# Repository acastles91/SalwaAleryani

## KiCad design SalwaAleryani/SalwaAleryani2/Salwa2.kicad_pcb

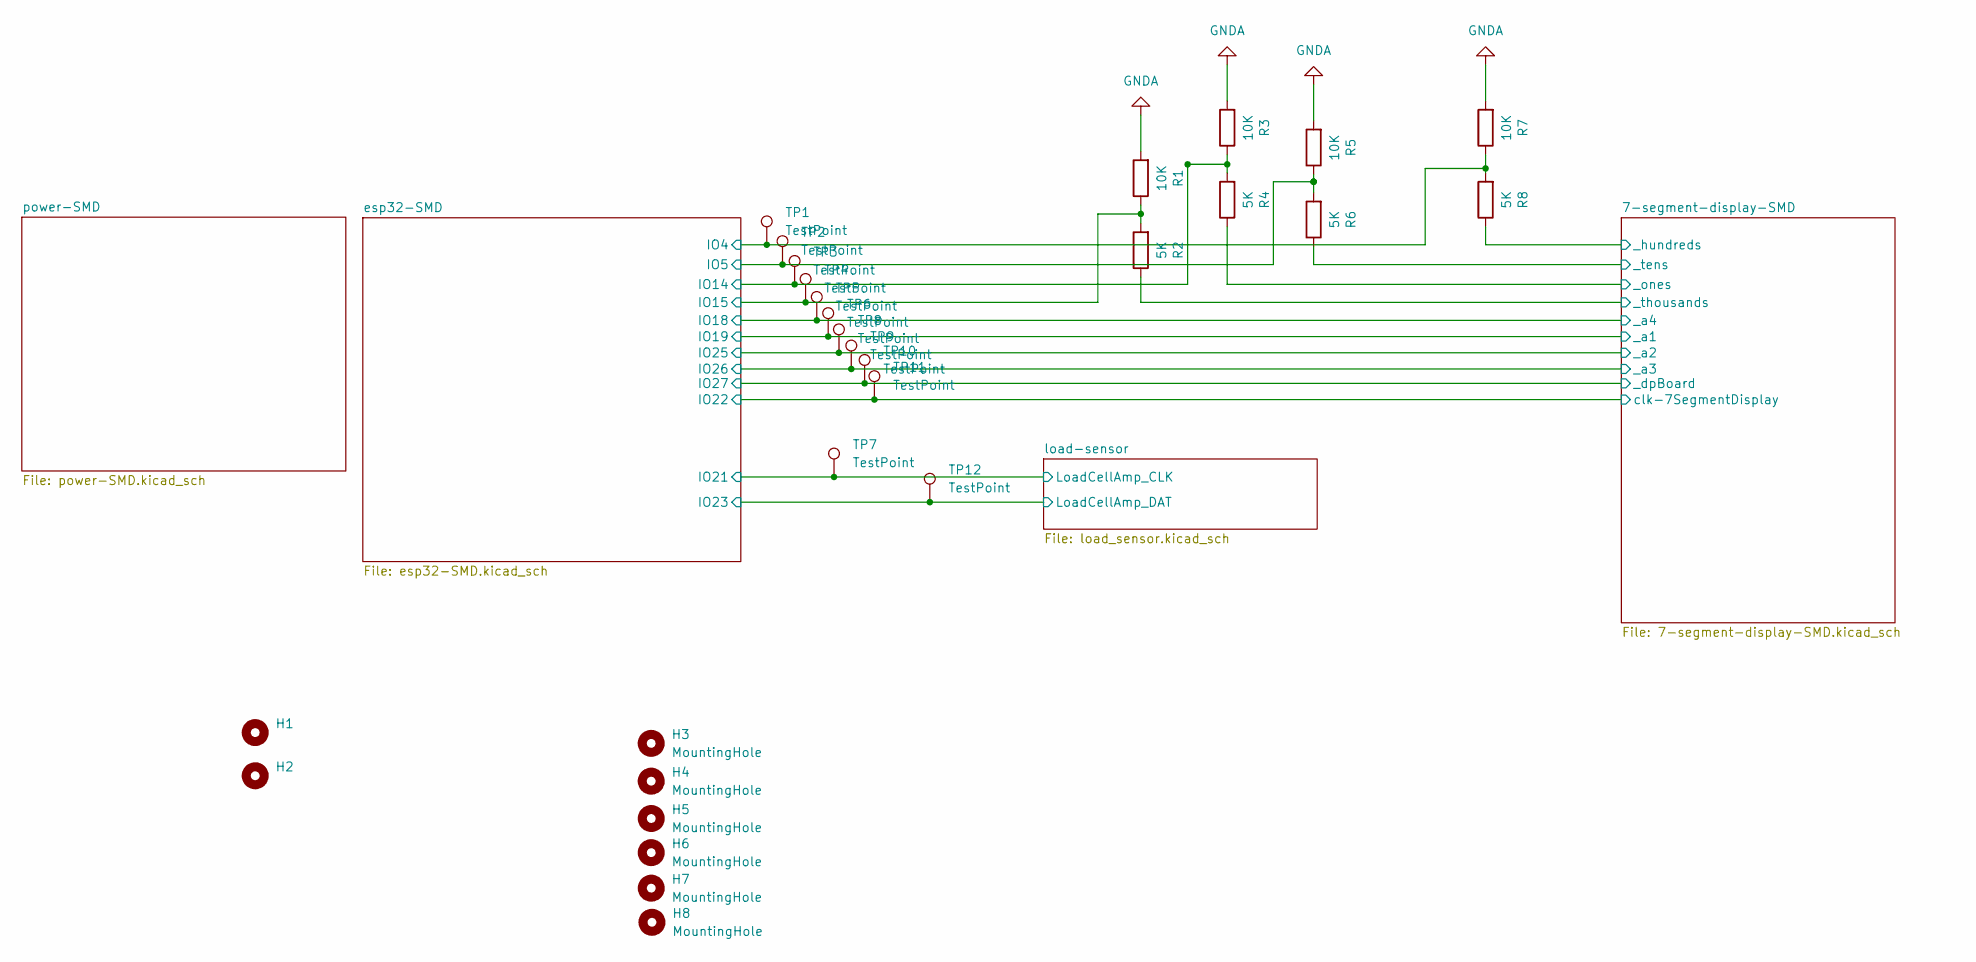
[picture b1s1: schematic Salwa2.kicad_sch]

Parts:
H1, H2: (no value)
H3, H4, H5, H6, H7, H8: MountingHole; MountingHole_4.3mm_M4_Pad_Via
R1, R3, R5, R7: 10K; R_1206_3216Metric_Pad1.30x1.75mm_HandSolder
R2, R4, R6, R8: 5K; R_1206_3216Metric_Pad1.30x1.75mm_HandSolder
TP1, TP2, TP3, TP4, TP5, TP6, TP7, TP8, TP9, TP10, TP11, TP12: TestPoint; TestPoint_Loop_D2.50mm_Drill1.85mm

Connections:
/7-segment-display-SMD/BCD_in1: TP6.1; also elsewhere on the board
/7-segment-display-SMD/BCD_in2: TP8.1; also elsewhere on the board
/7-segment-display-SMD/BCD_in3: TP9.1; also elsewhere on the board
/7-segment-display-SMD/BCD_in4: TP5.1; also elsewhere on the board
/7-segment-display-SMD/_dpBoard: TP10.1; also elsewhere on the board
/7-segment-display-SMD/_hundreds: R8.1; also elsewhere on the board
/7-segment-display-SMD/_ones: R4.1; also elsewhere on the board
/7-segment-display-SMD/_tens: R6.1; also elsewhere on the board
/7-segment-display-SMD/_thousands: R2.1; also elsewhere on the board
/7-segment-display-SMD/clk-7SegmentDisplay: TP11.1; also elsewhere on the board
/esp32-SMD/IO4: R7.1, R8.2, TP1.1; also elsewhere on the board
/esp32-SMD/IO5: R5.1, R6.2, TP2.1; also elsewhere on the board
/esp32-SMD/IO14: R3.1, R4.2, TP3.1; also elsewhere on the board
/esp32-SMD/IO15: R1.1, R2.2, TP4.1; also elsewhere on the board
/esp32-SMD/IO21: TP7.1; also elsewhere on the board
/esp32-SMD/IO23: TP12.1; also elsewhere on the board
GNDA: R1.2, R3.2, R5.2, R7.2; also elsewhere on the board

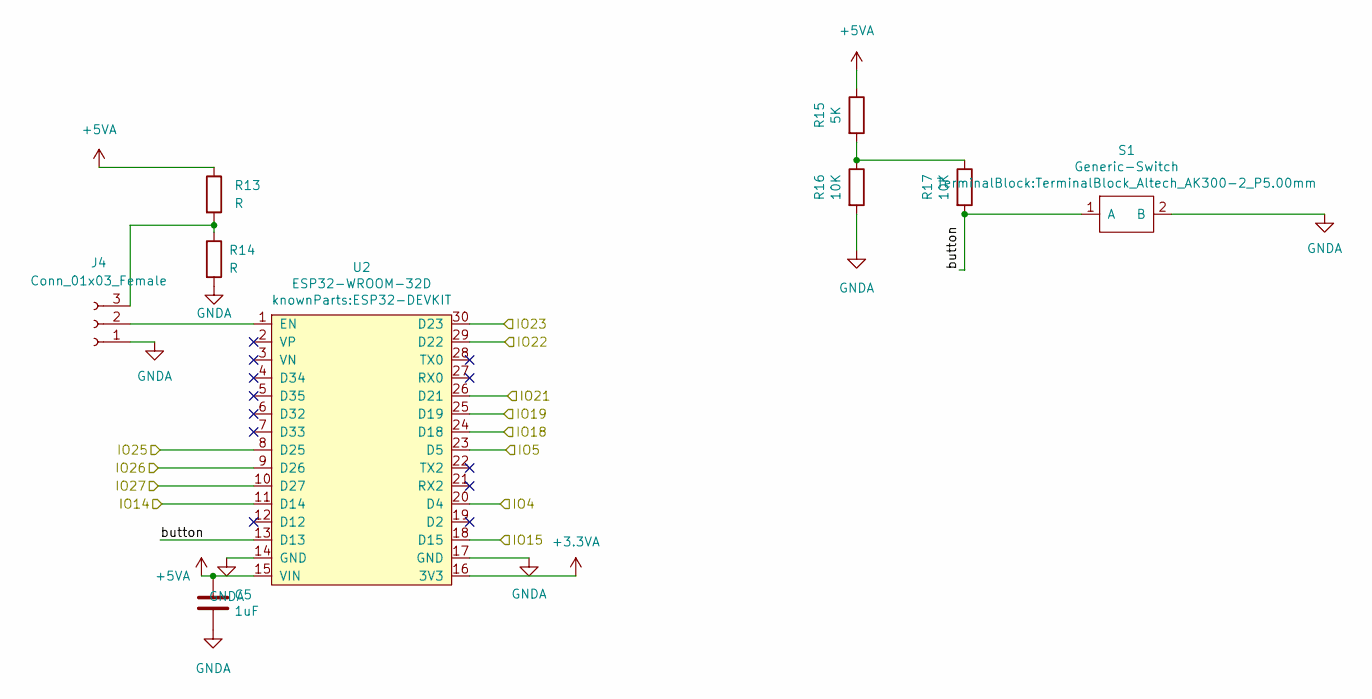
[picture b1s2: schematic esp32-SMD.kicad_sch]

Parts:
C5: 1uF; C_1210_3225Metric_Pad1.33x2.70mm_HandSolder
J4: Conn_01x03_Female; PinHeader_1x03_P2.54mm_Vertical
R13, R14: R; R_1206_3216Metric_Pad1.30x1.75mm_HandSolder
R15: 5K; R_1206_3216Metric_Pad1.30x1.75mm_HandSolder
R16, R17: 10K; R_1206_3216Metric_Pad1.30x1.75mm_HandSolder
S1: Generic-Switch; TerminalBlock_Altech_AK300-2_P5.00mm
U2: ESP32-WROOM-32D; ESP32-DEVKIT

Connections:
+3.3VA: U2.16 (3V3); also elsewhere on the board
+5VA: C5.1, R13.1, R15.1, U2.15 (VIN); also elsewhere on the board
/7-segment-display-SMD/BCD_in1: U2.25 (D19); also elsewhere on the board
/7-segment-display-SMD/BCD_in2: U2.8 (D25); also elsewhere on the board
/7-segment-display-SMD/BCD_in3: U2.9 (D26); also elsewhere on the board
/7-segment-display-SMD/BCD_in4: U2.24 (D18); also elsewhere on the board
/7-segment-display-SMD/_dpBoard: U2.10 (D27); also elsewhere on the board
/7-segment-display-SMD/clk-7SegmentDisplay: U2.29 (D22); also elsewhere on the board
/esp32-SMD/IO4: U2.20 (D4); also elsewhere on the board
/esp32-SMD/IO5: U2.23 (D5); also elsewhere on the board
/esp32-SMD/IO14: U2.11 (D14); also elsewhere on the board
/esp32-SMD/IO15: U2.18 (D15); also elsewhere on the board
/esp32-SMD/IO21: U2.26 (D21); also elsewhere on the board
/esp32-SMD/IO23: U2.30 (D23); also elsewhere on the board
/esp32-SMD/button: R17.2, S1.1 (A), U2.13 (D13)
GNDA: C5.2, J4.1, R14.2, R16.2, S1.2 (B), U2.14 (GND), U2.17 (GND); also elsewhere on the board
unnamed: J4.2, U2.1 (EN)
unnamed: J4.3, R13.2, R14.1
unnamed: R15.2, R16.1, R17.1

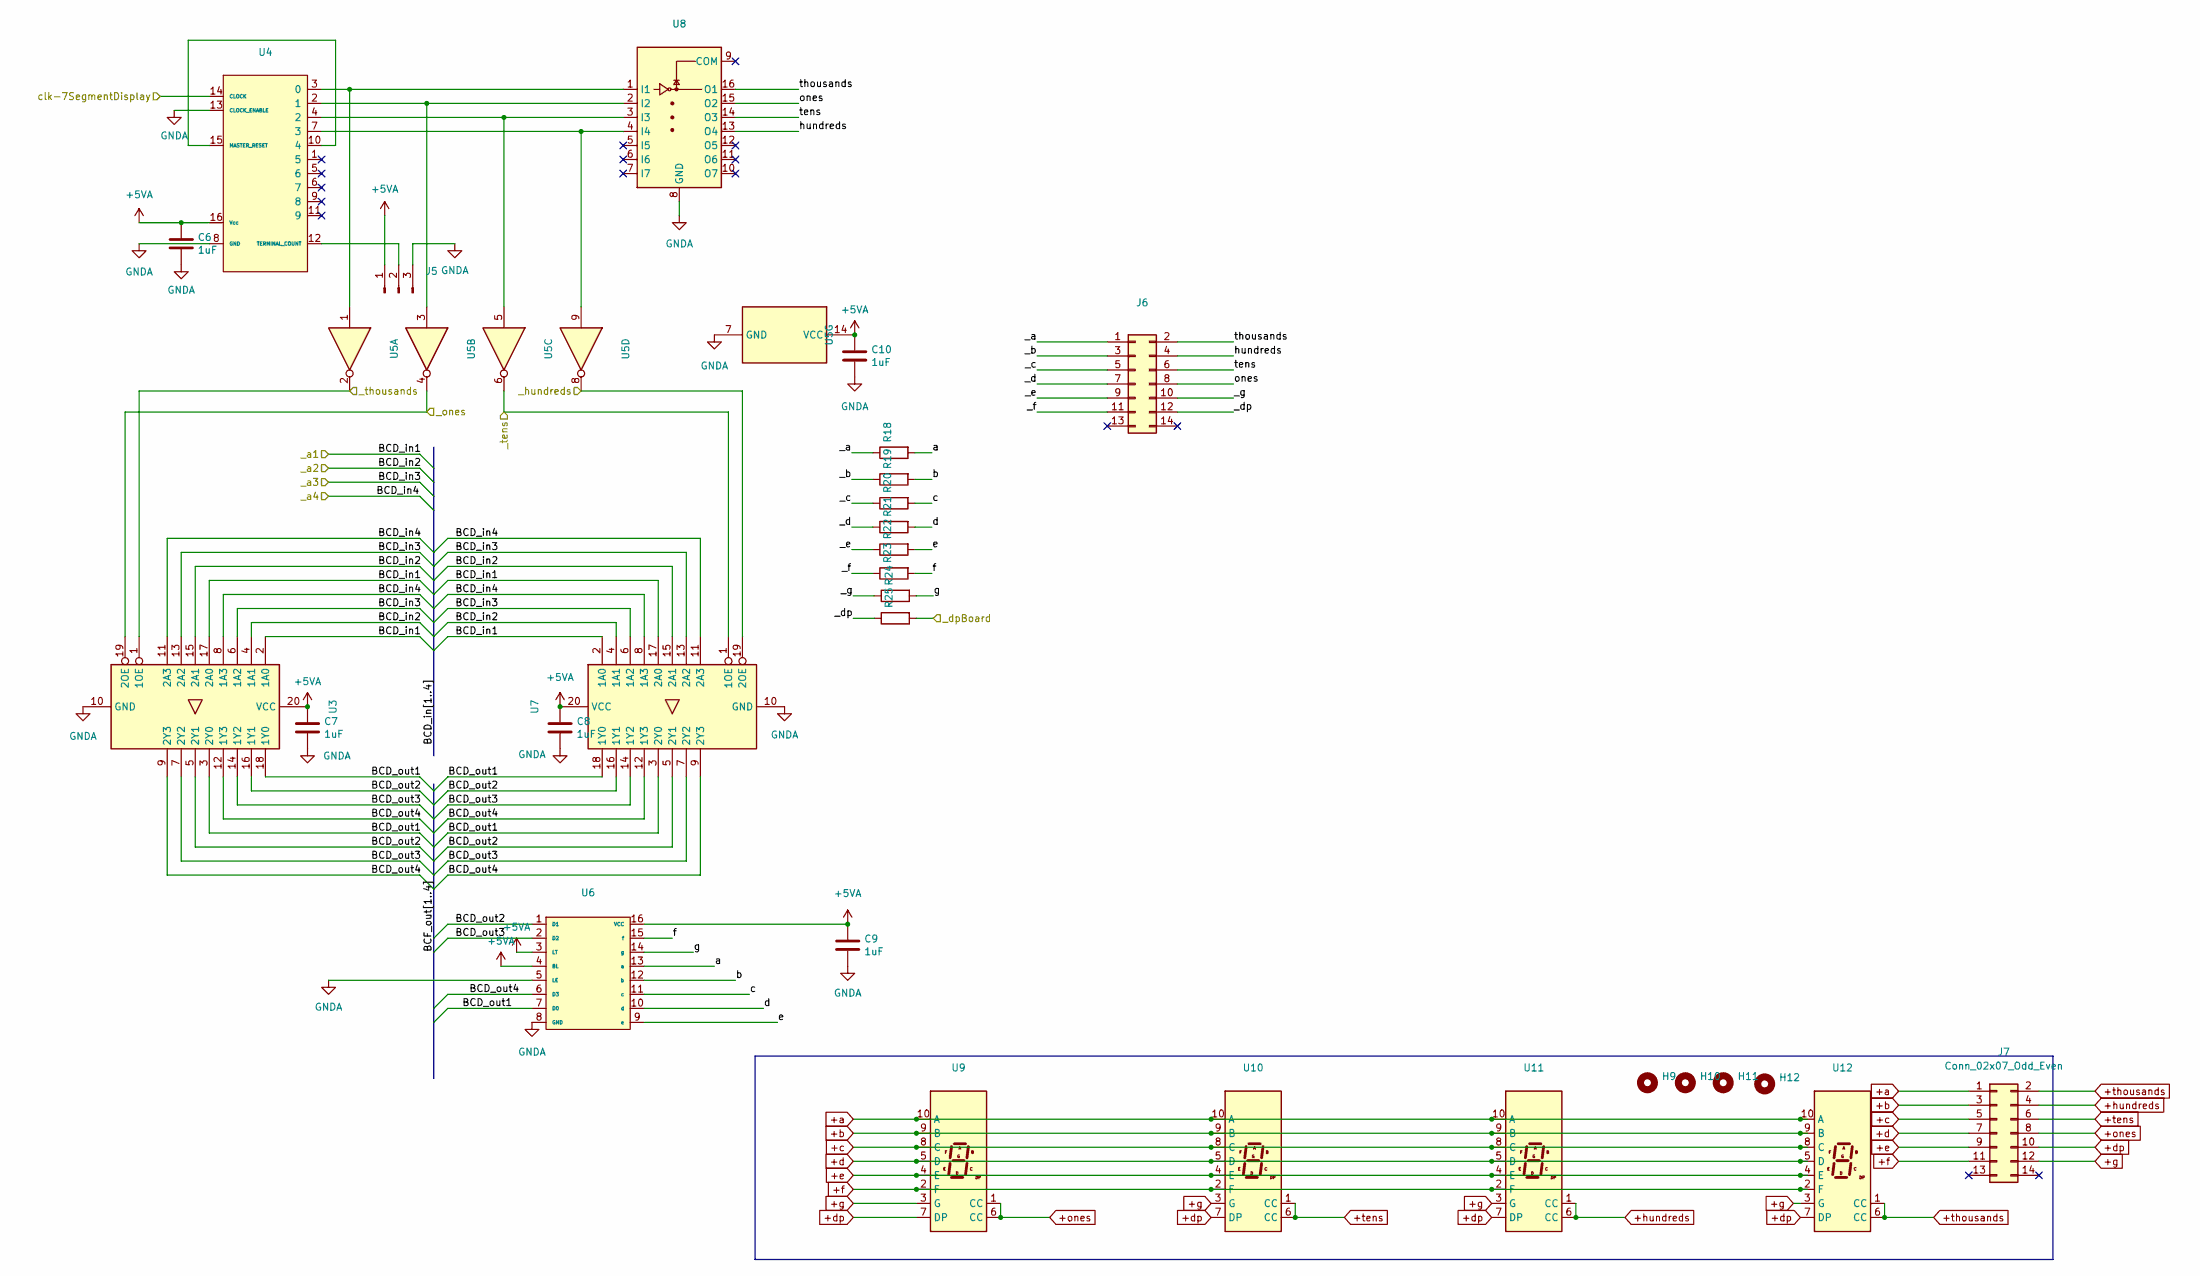
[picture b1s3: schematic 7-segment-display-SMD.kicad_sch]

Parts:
C6, C7, C8, C9, C10: 1uF; C_1210_3225Metric_Pad1.33x2.70mm_HandSolder
H9, H10, H11, H12: MountingHole_4.3mm_M4_Pad_Via
J5: PinHeader_1x03_P2.54mm_Vertical
J6: PinSocket_2x07_P2.54mm_Vertical
J7: Conn_02x07_Odd_Even; PinSocket_2x07_P2.54mm_Vertical
R18, R19, R20, R21, R22, R23, R24, R25: R_1206_3216Metric_Pad1.30x1.75mm_HandSolder
U3, U7: SOIC-20W_7.5x12.8mm_P1.27mm; DigiKey-Part-Number MC74HCT244ADWR2GOSCT-ND
U4: SOIC-16W_5.3x10.2mm_P1.27mm; DigiKey-Part-Number 296-12808-1-ND
U5: SOIC-14_3.9x8.7mm_P1.27mm
U6: SOIC-16_3.9x9.9mm_P1.27mm; DigiKey-Part-Number 296-32073-1-ND
U8: SOIC-16_3.9x9.9mm_P1.27mm; DigiKey-Part-Number ULN2003ADR2GOSCT-ND
U9, U10, U11, U12: HDSP-7507

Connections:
+5VA: C6.1, C7.1, C8.1, C9.1, C10.1, J5.1, U3.20 (VCC), U4.16 (Vcc), U5.14 (VCC), U6.3 (LT), U6.4 (BL), U6.16 (VCC), U7.20 (VCC); also elsewhere on the board
+a: J7.1, U9.10 (A), U10.10 (A), U11.10 (A), U12.10 (A)
+b: J7.3, U9.9 (B), U10.9 (B), U11.9 (B), U12.9 (B)
+c: J7.5, U9.8 (C), U10.8 (C), U11.8 (C), U12.8 (C)
+d: J7.7, U9.5 (D), U10.5 (D), U11.5 (D), U12.5 (D)
+dp: J7.10, U9.7 (DP), U10.7 (DP), U11.7 (DP), U12.7 (DP)
+e: J7.9, U9.4 (E), U10.4 (E), U11.4 (E), U12.4 (E)
+f: J7.11, U9.2 (F), U10.2 (F), U11.2 (F), U12.2 (F)
+g: J7.12, U9.3 (G), U10.3 (G), U11.3 (G), U12.3 (G)
+hundreds: J7.4, U11.1 (CC), U11.6 (CC)
+ones: J7.8, U9.1 (CC), U9.6 (CC)
+tens: J7.6, U10.1 (CC), U10.6 (CC)
+thousands: J7.2, U12.1 (CC), U12.6 (CC)
/7-segment-display-SMD/BCD_in1: U3.2 (1A0), U3.17 (2A0), U7.2 (1A0), U7.17 (2A0); also elsewhere on the board
/7-segment-display-SMD/BCD_in2: U3.4 (1A1), U3.15 (2A1), U7.4 (1A1), U7.15 (2A1); also elsewhere on the board
/7-segment-display-SMD/BCD_in3: U3.6 (1A2), U3.13 (2A2), U7.6 (1A2), U7.13 (2A2); also elsewhere on the board
/7-segment-display-SMD/BCD_in4: U3.8 (1A3), U3.11 (2A3), U7.8 (1A3), U7.11 (2A3); also elsewhere on the board
/7-segment-display-SMD/BCD_out1: U3.3 (2Y0), U3.18 (1Y0), U6.7 (D0), U7.3 (2Y0), U7.18 (1Y0)
/7-segment-display-SMD/BCD_out2: U3.5 (2Y1), U3.16 (1Y1), U6.1 (D1), U7.5 (2Y1), U7.16 (1Y1)
/7-segment-display-SMD/BCD_out3: U3.7 (2Y2), U3.14 (1Y2), U6.2 (D2), U7.7 (2Y2), U7.14 (1Y2)
/7-segment-display-SMD/BCD_out4: U3.9 (2Y3), U3.12 (1Y3), U6.6 (D3), U7.9 (2Y3), U7.12 (1Y3)
/7-segment-display-SMD/_a: J6.1, R18.1
/7-segment-display-SMD/_b: J6.3, R19.1
/7-segment-display-SMD/_c: J6.5, R20.1
/7-segment-display-SMD/_d: J6.7, R21.1
/7-segment-display-SMD/_dp: J6.12, R25.1
/7-segment-display-SMD/_dpBoard: R25.2; also elsewhere on the board
/7-segment-display-SMD/_e: J6.9, R22.1
/7-segment-display-SMD/_f: J6.11, R23.1
/7-segment-display-SMD/_g: J6.10, R24.1
/7-segment-display-SMD/_hundreds: U5.8, U7.19 (2OE); also elsewhere on the board
/7-segment-display-SMD/_ones: U3.19 (2OE), U5.4; also elsewhere on the board
/7-segment-display-SMD/_tens: U5.6, U7.1 (1OE); also elsewhere on the board
/7-segment-display-SMD/_thousands: U3.1 (1OE), U5.2; also elsewhere on the board
/7-segment-display-SMD/a: R18.2, U6.13 (a)
/7-segment-display-SMD/b: R19.2, U6.12 (b)
/7-segment-display-SMD/c: R20.2, U6.11 (c)
/7-segment-display-SMD/clk-7SegmentDisplay: U4.14 (CLOCK); also elsewhere on the board
/7-segment-display-SMD/d: R21.2, U6.10 (d)
/7-segment-display-SMD/e: R22.2, U6.9 (e)
/7-segment-display-SMD/f: R23.2, U6.15 (f)
/7-segment-display-SMD/g: R24.2, U6.14 (g)
/7-segment-display-SMD/hundreds: J6.4, U8.13 (O4)
/7-segment-display-SMD/ones: J6.8, U8.15 (O2)
/7-segment-display-SMD/tens: J6.6, U8.14 (O3)
/7-segment-display-SMD/thousands: J6.2, U8.16 (O1)
GNDA: C6.2, C7.2, C8.2, C9.2, C10.2, J5.3, U3.10 (GND), U4.8 (GND), U4.13 (CLOCK_ENABLE), U5.7 (GND), U6.5 (LE), U6.8 (GND), U7.10 (GND), U8.8 (GND); also elsewhere on the board
unnamed: J5.2, U4.12 (TERMINAL_COUNT)
unnamed: U4.2 (1), U5.3, U8.2 (I2)
unnamed: U4.3 (0), U5.1, U8.1 (I1)
unnamed: U4.4 (2), U5.5, U8.3 (I3)
unnamed: U4.7 (3), U5.9, U8.4 (I4)
unnamed: U4.10 (4), U4.15 (MASTER_RESET)

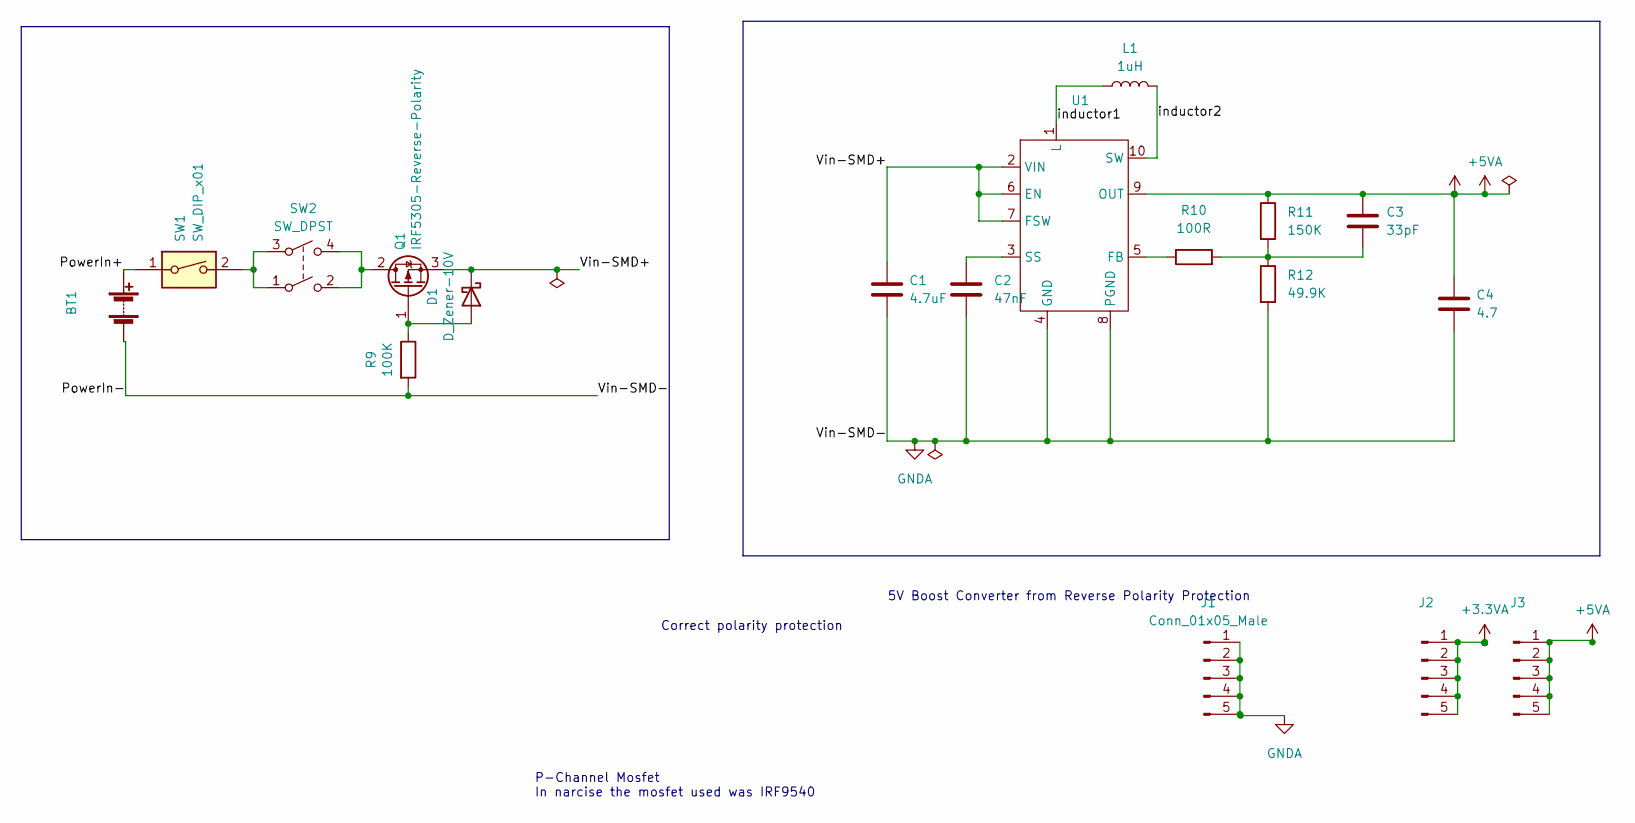
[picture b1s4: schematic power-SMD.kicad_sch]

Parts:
BT1: 1012
C1: 4.7uF; C_1206_3216Metric_Pad1.33x1.80mm_HandSolder
C2: 47nF; C_0603_1608Metric_Pad1.08x0.95mm_HandSolder
C3: 33pF; C_1206_3216Metric_Pad1.33x1.80mm_HandSolder
C4: 4.7; C_1206_3216Metric_Pad1.33x1.80mm_HandSolder
D1: D_Zener-10V; D_0603_1608Metric_Pad1.05x0.95mm_HandSolder
J1: Conn_01x05_Male; PinHeader_1x05_P2.54mm_Vertical
J2, J3: PinHeader_1x05_P2.54mm_Vertical
L1: 1uH; Sumida-1uH-Inductor
Q1: IRF5305-Reverse-Polarity; TO-263-3_TabPin2
R9: 100K; R_1206_3216Metric_Pad1.30x1.75mm_HandSolder
R10: 100R; R_1206_3216Metric_Pad1.30x1.75mm_HandSolder
R11: 150K; R_1206_3216Metric_Pad1.30x1.75mm_HandSolder
R12: 49.9K; R_1206_3216Metric_Pad1.30x1.75mm_HandSolder
SW1: SW_DIP_x01; JST_XH_B2B-XH-AM_1x02_P2.50mm_Vertical
SW2: SW_DPST; PVA1 EE H1 3.5N V2 Switch; DigiKey-Part-Number 108-PVA1EEH13.5NV2-ND
U1: VSON-10-1EP_3x3mm_P0.5mm_EP1.65x2.4mm_ThermalVias

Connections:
+3.3VA: J2.1, J2.2, J2.3, J2.4, J2.5; also elsewhere on the board
+5VA: C3.1, C4.1, J3.1, J3.2, J3.3, J3.4, J3.5, R11.1, U1.9 (OUT); also elsewhere on the board
/power-SMD/PowerIn+: BT1.1 (+), SW1.1
/power-SMD/Vin-SMD+: C1.1, D1.1 (K), Q1.3 (S), U1.2 (VIN), U1.6 (EN), U1.7 (FSW)
/power-SMD/inductor1: L1.1, U1.1 (L)
/power-SMD/inductor2: L1.2, U1.10 (SW)
GNDA: BT1.2 (-), C1.2, C2.2, C4.2, J1.1, J1.2, J1.3, J1.4, J1.5, R9.2, R12.2, U1.4 (GND), U1.8 (PGND); also elsewhere on the board
unnamed: C2.1, U1.3 (SS)
unnamed: C3.2, R10.2, R11.2, R12.1
unnamed: D1.2 (A), Q1.1 (G), R9.1
unnamed: Q1.2 (D), SW2.2, SW2.4
unnamed: R10.1, U1.5 (FB)
unnamed: SW1.2, SW2.1, SW2.3

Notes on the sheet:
Correct polarity protection
P-Channel Mosfet In narcise the mosfet used was IRF9540
5V Boost Converter from Reverse Polarity Protection

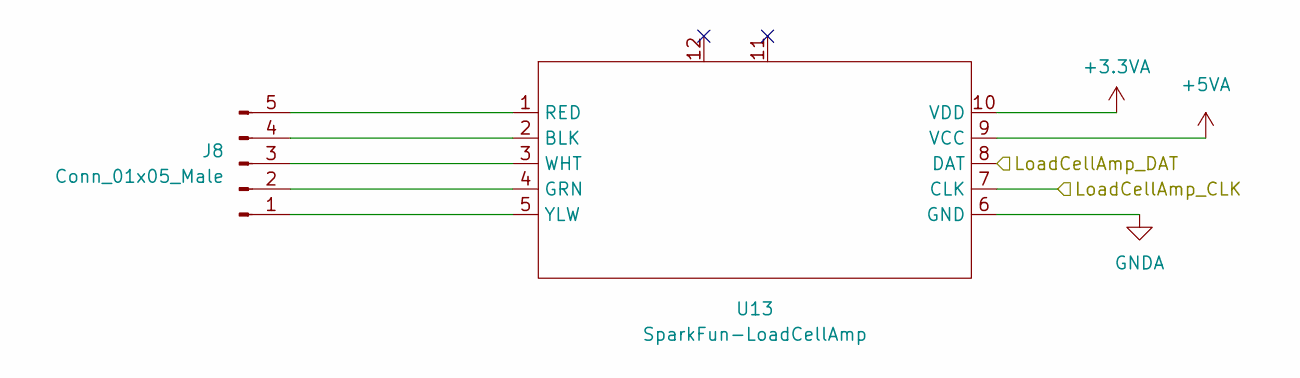
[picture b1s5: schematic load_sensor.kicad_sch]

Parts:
J8: Conn_01x05_Male; Molex_Micro-Fit_3.0_43650-0500_1x05_P3.00mm_Horizontal; DigiKey-Part-Number 900-2157602005-ND
U13: SparkFun-LoadCellAmp; Outline-LoadCellAmp

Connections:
+3.3VA: U13.10 (VDD); also elsewhere on the board
+5VA: U13.9 (VCC); also elsewhere on the board
/esp32-SMD/IO21: U13.7 (CLK); also elsewhere on the board
/esp32-SMD/IO23: U13.8 (DAT); also elsewhere on the board
GNDA: U13.6 (GND); also elsewhere on the board
unnamed: J8.1, U13.5 (YLW)
unnamed: J8.2, U13.4 (GRN)
unnamed: J8.3, U13.3 (WHT)
unnamed: J8.4, U13.2 (BLK)
unnamed: J8.5, U13.1 (RED)

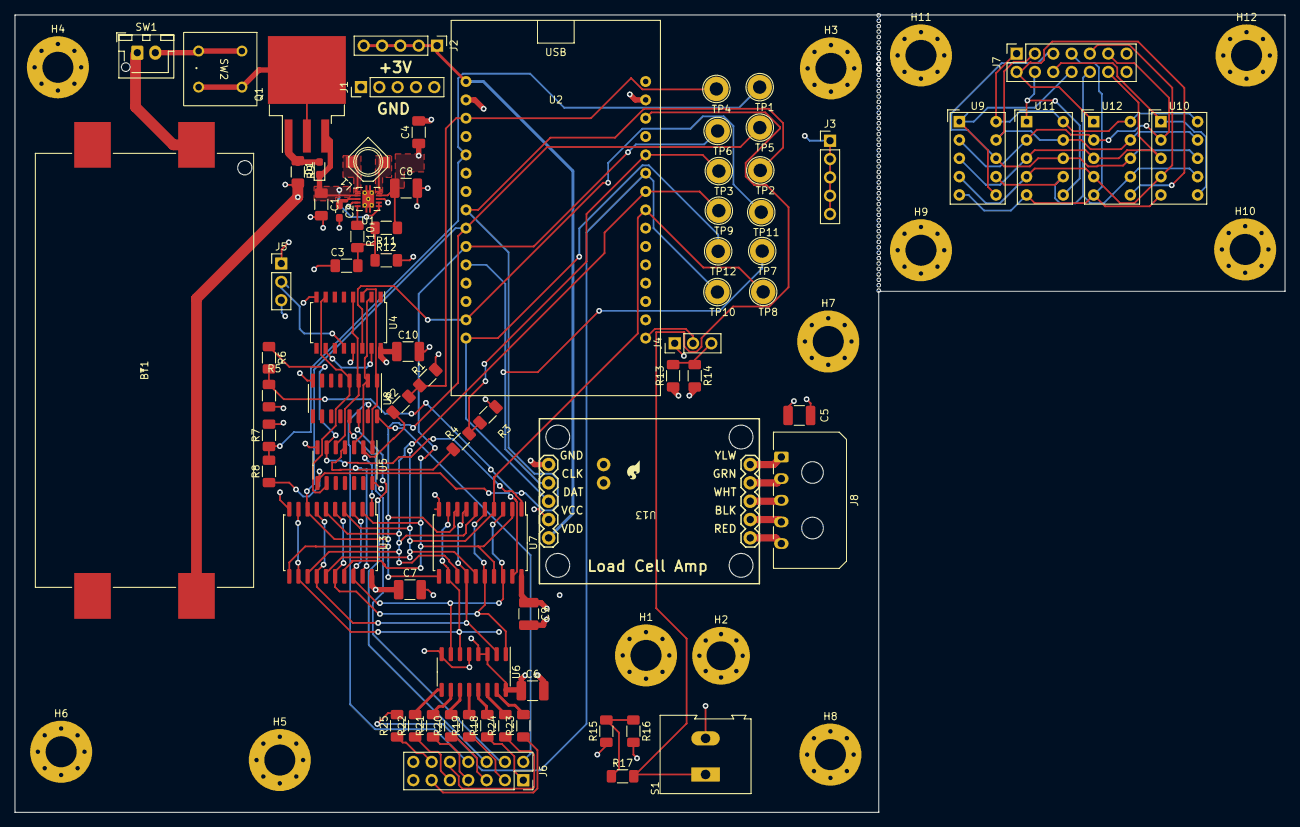
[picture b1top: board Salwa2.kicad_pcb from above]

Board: 4 copper layers, 176.0 x 110.5 mm, 87 parts (0 on the bottom side), 79 nets.

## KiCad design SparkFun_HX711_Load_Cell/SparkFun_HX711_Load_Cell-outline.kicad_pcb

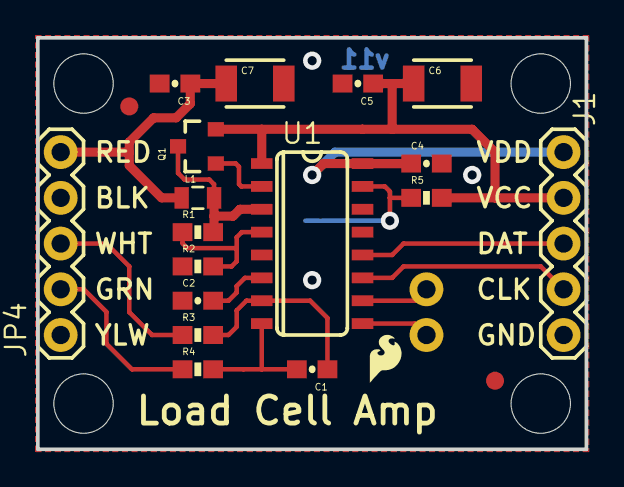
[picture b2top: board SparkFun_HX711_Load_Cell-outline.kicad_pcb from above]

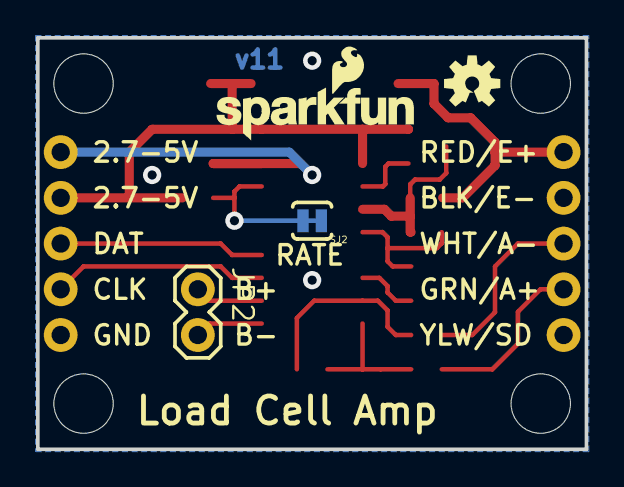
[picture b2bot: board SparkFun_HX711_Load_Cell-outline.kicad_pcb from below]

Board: 2 copper layers, 30.5 x 22.9 mm, 30 parts (4 on the bottom side), 17 nets.

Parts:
C1, C2, C3, C4, C5: 0.1uF; 0603-CAP
C6, C7: 10uF; 1210
FID1, FID2: FIDUCIAL1X2; FIDUCIAL-1X2
FRAME1: FRAME-LETTER; CREATIVE_COMMONS
J1: 1X05
JP2: 1X02
JP4: 1X05
L1: 3.3uH; 0805
LOGO1: SFE_LOGO_NAME_FLAME.1_INCH; SFE_LOGO_NAME_FLAME_.1
LOGO3: SFE_LOGO_FLAME.1_INCH; SFE_LOGO_FLAME_.1
Q1: MMBT4403; SOT23-3
R1: 20k; 0603-RES
R2: 8.2K; 0603-RES
R3, R4: 100; 0603-RES
R5: 10K; 0603-RES
SJ2: PAD-JUMPER-2-NC_BY_TRACE_YES_SILK
STANDOFF1, STANDOFF2, STANDOFF3, STANDOFF4: STAND-OFF
U1: HX711; SO16
U7: OSHW-LOGOS; OSHW-LOGO-S
U$1: REVISION

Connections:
A+: JP4.2, R4.1
A-: JP4.3, R3.1
AVDD: C3.1, C7.1, JP4.5, L1.1
B+: JP2.1, U1.10
B-: JP2.2, U1.9
DAT: J1.3, U1.12
GND: C2.1, C3.2, C4.2, C5.2, C6.2, C7.2, J1.5, JP4.1, JP4.4, R2.1, SJ2.1, U1.5, U1.14
unnamed: R5.1, SJ2.2, U1.15
unnamed: C1.1, R3.2, U1.7
unnamed: C1.2, R4.2, U1.8
unnamed: Q1.1, U1.2
unnamed: L1.2, Q1.3, R1.2, U1.3
unnamed: R1.1, R2.2, U1.4
unnamed: C2.2, U1.6
SCK: J1.4, U1.11
VCC: C5.1, C6.1, J1.2, Q1.2, R5.2, U1.1
VDD: C4.1, J1.1, U1.16

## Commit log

2022-12-19 Didn't work the first time

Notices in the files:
parts and their libraries:
Copyright 2021 Accelerated Designs. All rights reserved.
HTTPS://CREATIVECOMMONS.ORG/LICENSES/BY-SA/4.0
RELEASED UNDER THE CREATIVE COMMONS ATTRIBUTION SHARE-ALIKE 4.0 LICENSE
